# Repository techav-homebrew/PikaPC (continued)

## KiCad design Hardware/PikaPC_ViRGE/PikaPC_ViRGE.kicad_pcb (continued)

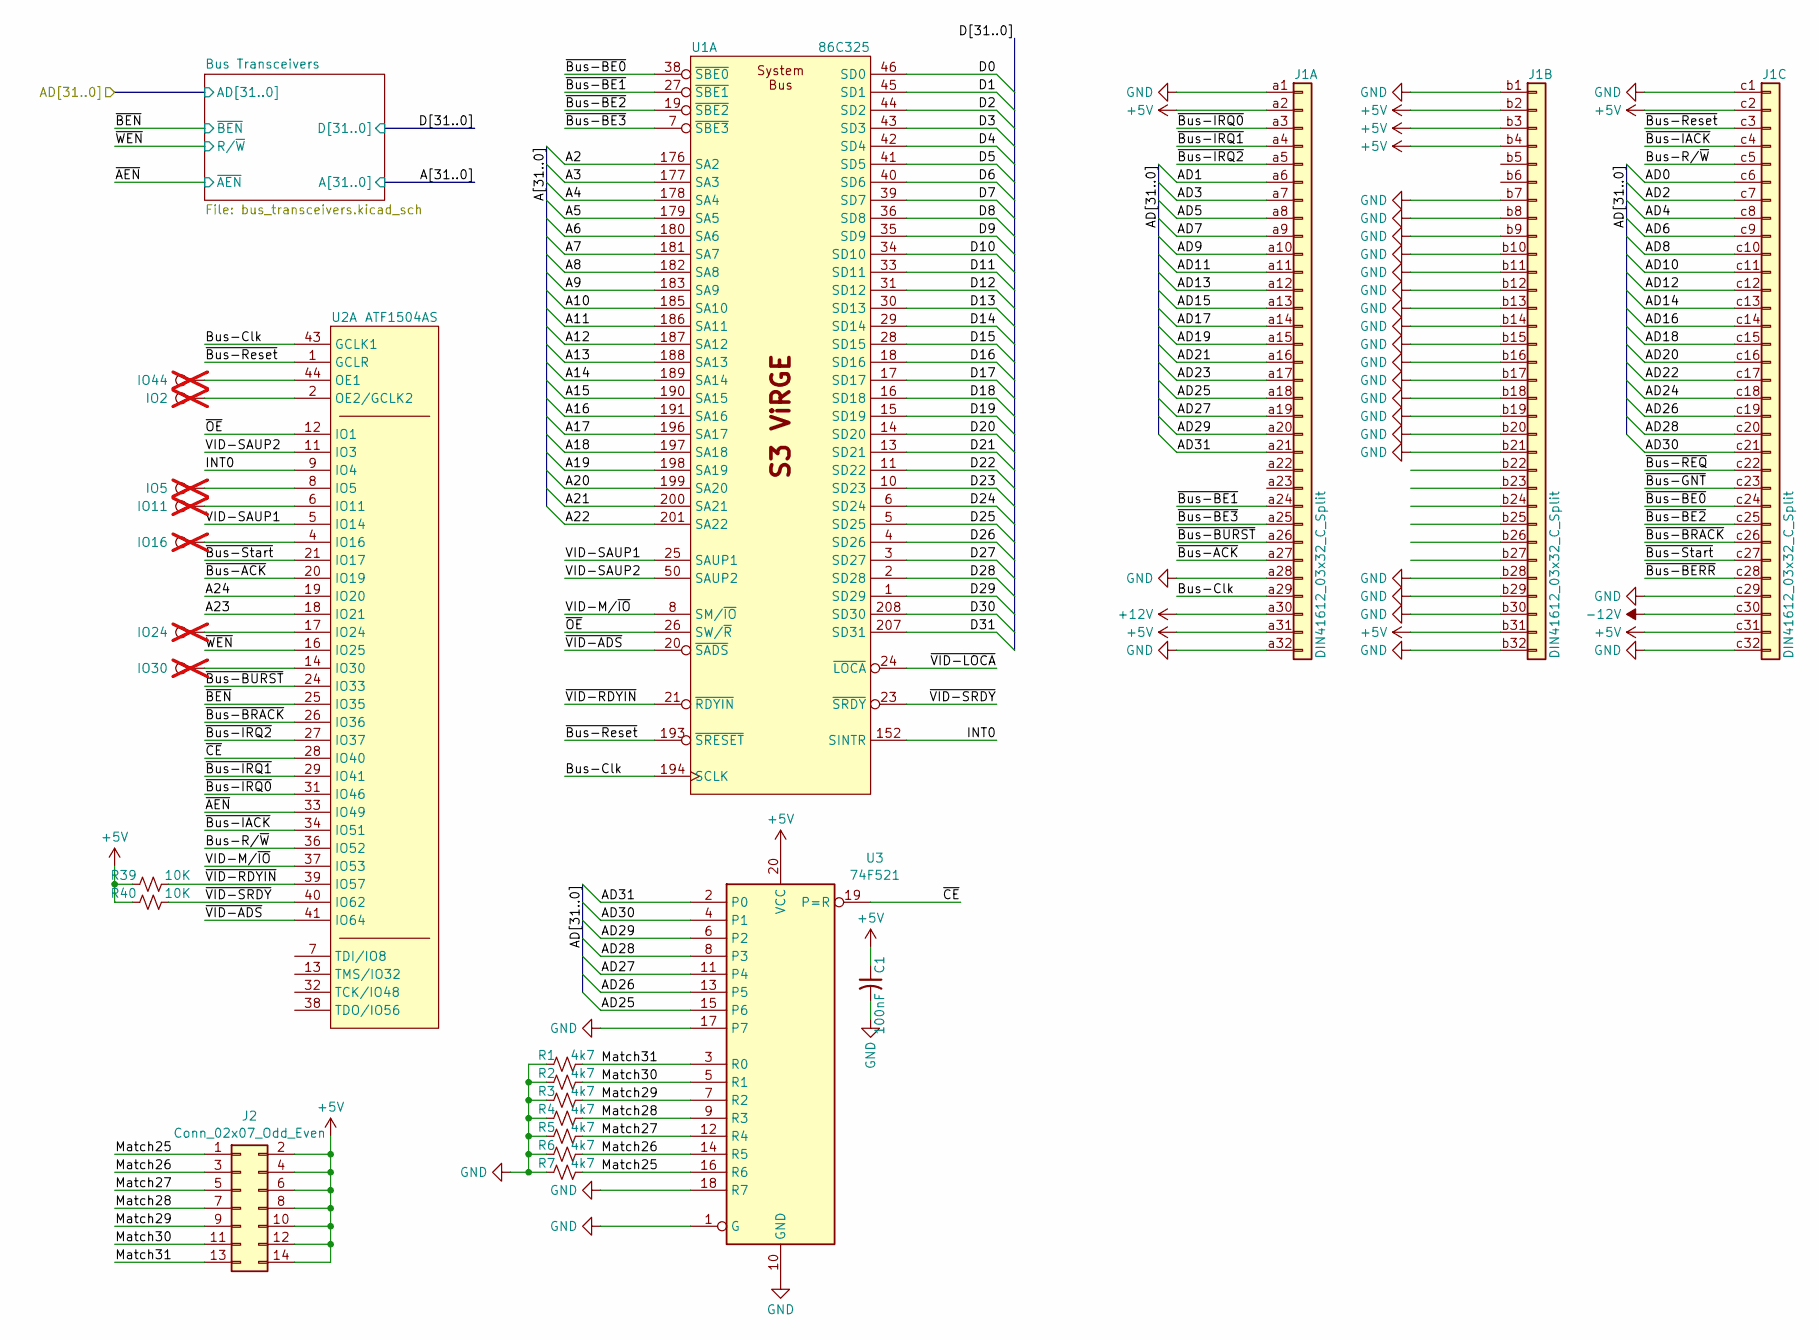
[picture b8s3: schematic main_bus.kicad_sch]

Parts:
C1: 100nF; C_0805_2012Metric; Mouser 187-CL21B104KACNNNC
IO2, IO5, IO11, IO16, IO24, IO30, IO44: TestPoint; PinHeader_1x01_P2.54mm_Vertical; not fitted
J1: DIN41612_03x32_C_Split; DIN41612_C_3x32_Male_Horizontal_THT
J2: Conn_02x07_Odd_Even; PinHeader_2x07_P2.54mm_Vertical
R1, R2, R3, R4, R5, R6, R7: 4k7; R_0805_2012Metric; Mouser 303-0805W8J0472T5E
R39, R40: 10K; R_0805_2012Metric; Mouser 303-0805S8J0103T5E
U1: 86C325; PQFP-208_28x28mm_P0.5mm
U2: ATF1504AS; PLCC-44_THT-Socket
U3: 74F521; SOIC-20W_7.5x12.8mm_P1.27mm; Mouser 595-SN74F521DWR

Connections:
+5V: C1.1, J1.a2, J1.a31, J1.b2, J1.b3, J1.b4, J1.b31, J1.c2, J1.c31, J2.2, J2.4, J2.6, J2.8, J2.10, J2.12, J2.14, R39.1, R40.1, U1.12 (Vdd), U1.37 (Vdd), U3.20 (VCC); also elsewhere on the board
+12V: J1.a30
-12V: J1.c30
/Main Bus/A2: U1.176 (SA2); also elsewhere on the board
/Main Bus/A3: U1.177 (SA3); also elsewhere on the board
/Main Bus/A4: U1.178 (SA4); also elsewhere on the board
/Main Bus/A5: U1.179 (SA5); also elsewhere on the board
/Main Bus/A6: U1.180 (SA6); also elsewhere on the board
/Main Bus/A7: U1.181 (SA7); also elsewhere on the board
/Main Bus/A8: U1.182 (SA8); also elsewhere on the board
/Main Bus/A9: U1.183 (SA9); also elsewhere on the board
/Main Bus/A10: U1.185 (SA10); also elsewhere on the board
/Main Bus/A11: U1.186 (SA11); also elsewhere on the board
/Main Bus/A12: U1.187 (SA12); also elsewhere on the board
/Main Bus/A13: U1.188 (SA13); also elsewhere on the board
/Main Bus/A14: U1.189 (SA14); also elsewhere on the board
/Main Bus/A15: U1.190 (SA15); also elsewhere on the board
/Main Bus/A16: U1.191 (SA16); also elsewhere on the board
/Main Bus/A17: U1.196 (SA17); also elsewhere on the board
/Main Bus/A18: U1.197 (SA18); also elsewhere on the board
/Main Bus/A19: U1.198 (SA19); also elsewhere on the board
/Main Bus/A20: U1.199 (SA20); also elsewhere on the board
/Main Bus/A21: U1.200 (SA21); also elsewhere on the board
/Main Bus/A22: U1.201 (SA22); also elsewhere on the board
/Main Bus/A23: U2.18 (IO21); also elsewhere on the board
/Main Bus/A24: U2.19 (IO20); also elsewhere on the board
/Main Bus/AD0: J1.c6; also elsewhere on the board
/Main Bus/AD1: J1.a6; also elsewhere on the board
/Main Bus/AD2: J1.c7; also elsewhere on the board
/Main Bus/AD3: J1.a7; also elsewhere on the board
/Main Bus/AD4: J1.c8; also elsewhere on the board
/Main Bus/AD5: J1.a8; also elsewhere on the board
/Main Bus/AD6: J1.c9; also elsewhere on the board
/Main Bus/AD7: J1.a9; also elsewhere on the board
/Main Bus/AD8: J1.c10; also elsewhere on the board
/Main Bus/AD9: J1.a10; also elsewhere on the board
/Main Bus/AD10: J1.c11; also elsewhere on the board
/Main Bus/AD11: J1.a11; also elsewhere on the board
/Main Bus/AD12: J1.c12; also elsewhere on the board
/Main Bus/AD13: J1.a12; also elsewhere on the board
/Main Bus/AD14: J1.c13; also elsewhere on the board
/Main Bus/AD15: J1.a13; also elsewhere on the board
/Main Bus/AD16: J1.c14; also elsewhere on the board
/Main Bus/AD17: J1.a14; also elsewhere on the board
/Main Bus/AD18: J1.c15; also elsewhere on the board
/Main Bus/AD19: J1.a15; also elsewhere on the board
/Main Bus/AD20: J1.c16; also elsewhere on the board
/Main Bus/AD21: J1.a16; also elsewhere on the board
/Main Bus/AD22: J1.c17; also elsewhere on the board
/Main Bus/AD23: J1.a17; also elsewhere on the board
/Main Bus/AD24: J1.c18; also elsewhere on the board
/Main Bus/AD25: J1.a18, U3.15 (P6); also elsewhere on the board
/Main Bus/AD26: J1.c19, U3.13 (P5); also elsewhere on the board
/Main Bus/AD27: J1.a19, U3.11 (P4); also elsewhere on the board
/Main Bus/AD28: J1.c20, U3.8 (P3); also elsewhere on the board
/Main Bus/AD29: J1.a20, U3.6 (P2); also elsewhere on the board
/Main Bus/AD30: J1.c21, U3.4 (P1); also elsewhere on the board
/Main Bus/AD31: J1.a21, U3.2 (P0); also elsewhere on the board
/Main Bus/Bus-Clk: J1.a29, U1.194 (SCLK), U2.43 (GCLK1)
/Main Bus/Bus-R/~W: J1.c5, U2.36 (IO52)
/Main Bus/D0: U1.46 (SD0); also elsewhere on the board
/Main Bus/D1: U1.45 (SD1); also elsewhere on the board
/Main Bus/D2: U1.44 (SD2); also elsewhere on the board
/Main Bus/D3: U1.43 (SD3); also elsewhere on the board
/Main Bus/D4: U1.42 (SD4); also elsewhere on the board
/Main Bus/D5: U1.41 (SD5); also elsewhere on the board
/Main Bus/D6: U1.40 (SD6); also elsewhere on the board
/Main Bus/D7: U1.39 (SD7); also elsewhere on the board
/Main Bus/D8: U1.36 (SD8); also elsewhere on the board
/Main Bus/D9: U1.35 (SD9); also elsewhere on the board
/Main Bus/D10: U1.34 (SD10); also elsewhere on the board
/Main Bus/D11: U1.33 (SD11); also elsewhere on the board
/Main Bus/D12: U1.31 (SD12); also elsewhere on the board
/Main Bus/D13: U1.30 (SD13); also elsewhere on the board
/Main Bus/D14: U1.29 (SD14); also elsewhere on the board
/Main Bus/D15: U1.28 (SD15); also elsewhere on the board
/Main Bus/D16: U1.18 (SD16); also elsewhere on the board
/Main Bus/D17: U1.17 (SD17); also elsewhere on the board
/Main Bus/D18: U1.16 (SD18); also elsewhere on the board
/Main Bus/D19: U1.15 (SD19); also elsewhere on the board
/Main Bus/D20: U1.14 (SD20); also elsewhere on the board
/Main Bus/D21: U1.13 (SD21); also elsewhere on the board
/Main Bus/D22: U1.11 (SD22); also elsewhere on the board
/Main Bus/D23: U1.10 (SD23); also elsewhere on the board
/Main Bus/D24: U1.6 (SD24); also elsewhere on the board
/Main Bus/D25: U1.5 (SD25); also elsewhere on the board
/Main Bus/D26: U1.4 (SD26); also elsewhere on the board
/Main Bus/D27: U1.3 (SD27); also elsewhere on the board
/Main Bus/D28: U1.2 (SD28); also elsewhere on the board
/Main Bus/D29: U1.1 (SD29); also elsewhere on the board
/Main Bus/D30: U1.208 (SD30); also elsewhere on the board
/Main Bus/D31: U1.207 (SD31); also elsewhere on the board
/Main Bus/INT0: U1.152 (SINTR), U2.9 (IO4)
/Main Bus/Match25: J2.1, R7.2, U3.16 (R6)
/Main Bus/Match26: J2.3, R6.2, U3.14 (R5)
/Main Bus/Match27: J2.5, R5.2, U3.12 (R4)
/Main Bus/Match28: J2.7, R4.2, U3.9 (R3)
/Main Bus/Match29: J2.9, R3.2, U3.7 (R2)
/Main Bus/Match30: J2.11, R2.2, U3.5 (R1)
/Main Bus/Match31: J2.13, R1.2, U3.3 (R0)
/Main Bus/VID-M/~IO: U1.8 (SM/~IO), U2.37 (IO53)
/Main Bus/VID-SAUP1: U1.25 (SAUP1), U2.5 (IO14)
/Main Bus/VID-SAUP2: U1.50 (SAUP2), U2.11 (IO3)
/Main Bus/~AEN: U2.33 (IO49); also elsewhere on the board
/Main Bus/~BEN: U2.25 (IO35); also elsewhere on the board
/Main Bus/~Bus-ACK: J1.a27, U2.20 (IO19)
/Main Bus/~Bus-BE0: J1.c24, U1.38 (~SBE0)
/Main Bus/~Bus-BE1: J1.a24, U1.27 (~SBE1)
/Main Bus/~Bus-BE2: J1.c25, U1.19 (~SBE2)
/Main Bus/~Bus-BE3: J1.a25, U1.7 (~SBE3)
/Main Bus/~Bus-BERR: J1.c28
/Main Bus/~Bus-BRACK: J1.c26, U2.26 (IO36)
/Main Bus/~Bus-BURST: J1.a26, U2.24 (IO33)
/Main Bus/~Bus-GNT: J1.c23
/Main Bus/~Bus-IACK: J1.c4, U2.34 (IO51)
/Main Bus/~Bus-IRQ0: J1.a3, U2.31 (IO46)
/Main Bus/~Bus-IRQ1: J1.a4, U2.29 (IO41)
/Main Bus/~Bus-IRQ2: J1.a5, U2.27 (IO37)
/Main Bus/~Bus-REQ: J1.c22
/Main Bus/~Bus-Reset: J1.c3, U1.193 (~SRESET), U2.1 (GCLR)
/Main Bus/~Bus-Start: J1.c27, U2.21 (IO17)
/Main Bus/~CE: U2.28 (IO40), U3.19 (P=R)
/Main Bus/~OE: U1.26 (SW/~R), U2.12 (IO1)
/Main Bus/~VID-ADS: U1.20 (~SADS), U2.41 (IO64)
/Main Bus/~VID-LOCA: U1.24 (~LOCA); also elsewhere on the board
/Main Bus/~VID-RDYIN: R39.2, U1.21 (~RDYIN), U2.39 (IO57)
/Main Bus/~VID-SRDY: R40.2, U1.23 (~SRDY), U2.40 (IO62)
/Main Bus/~WEN: U2.16 (IO25); also elsewhere on the board
GND: C1.2, J1.a1, J1.a28, J1.a32, J1.b1, J1.b7, J1.b8, J1.b9, J1.b10, J1.b11, J1.b12, J1.b13, J1.b14, J1.b15, J1.b16, J1.b17, J1.b18, J1.b19, J1.b20, J1.b21, J1.b28, J1.b29, J1.b30, J1.b32, J1.c1, J1.c29, J1.c32, R1.1, R2.1, R3.1, R4.1, R5.1, R6.1, R7.1, U1.9 (Vss), U1.32 (Vss), U3.1 (G), U3.10 (GND), U3.17 (P7), U3.18 (R7); also elsewhere on the board
unnamed: IO5.1, U2.8 (IO5)
unnamed: IO11.1, U2.6 (IO11)
unnamed: IO16.1, U2.4 (IO16)
unnamed: IO24.1, U2.17 (IO24)
unnamed: IO30.1, U2.14 (IO30)
unnamed: IO44.1, U2.44 (OE1)
unnamed: IO2.1, U2.2 (OE2/GCLK2)

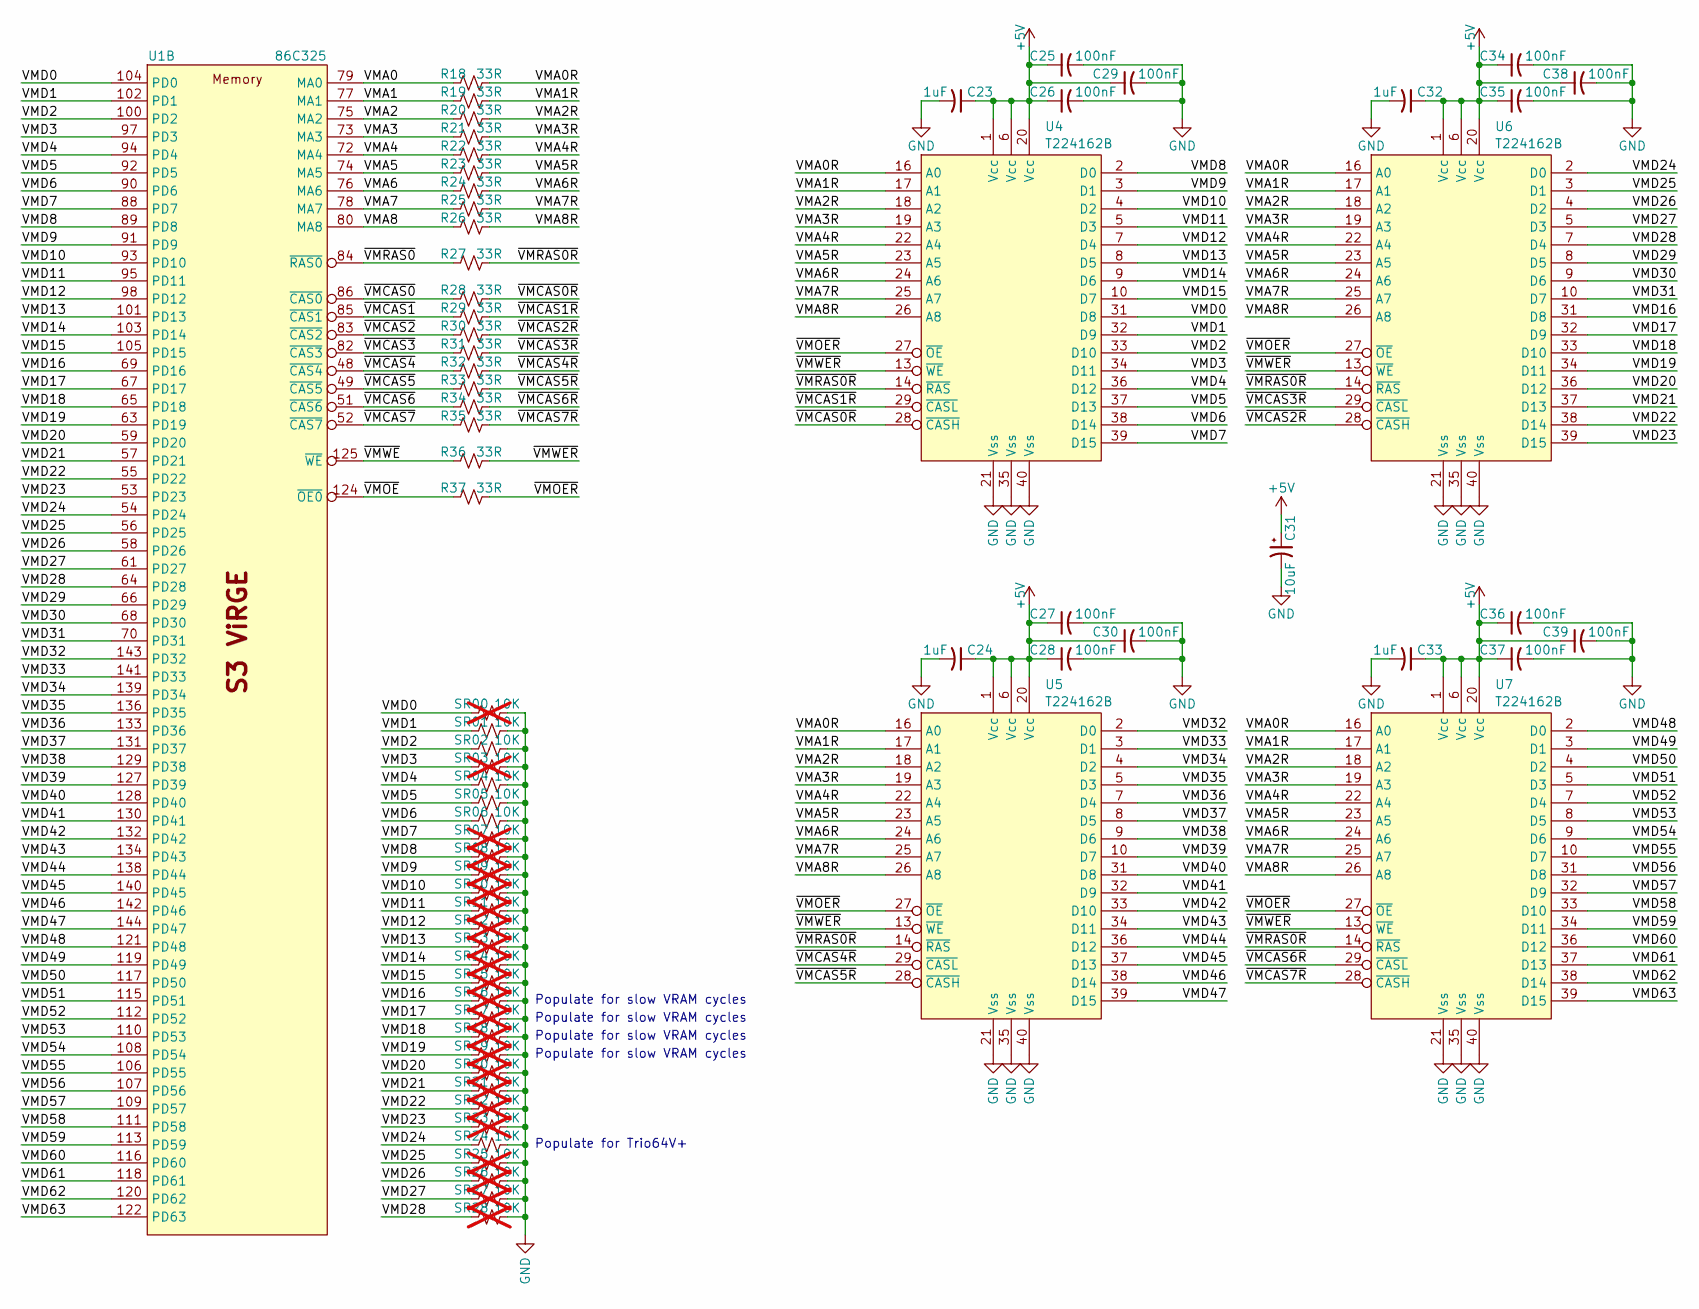
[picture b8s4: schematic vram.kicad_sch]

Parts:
C23, C24, C32, C33: 1uF; C_0805_2012Metric
C25, C26, C27, C28, C29, C30, C34, C35, C36, C37, C38, C39: 100nF; C_0805_2012Metric
C31: 10uF; CP_Elec_4x5.7; Mouser 80-EDK106M016A9BAA
R18, R19, R20, R21, R22, R23, R24, R25, R26, R27, R28, R29, R30, R31, R32, R33, R34, R35, R36, R37: 33R; R_0805_2012Metric
SR00, SR03, SR07, SR08, SR09, SR10, SR11, SR12, SR13, SR14, SR15, SR16, SR17, SR18, SR19, SR20, SR21, SR22, SR23, SR25, SR26, SR27, SR28: 10K; R_0805_2012Metric; not fitted
SR01, SR02, SR04, SR05, SR06, SR24: 10K; R_0805_2012Metric
U1: 86C325; PQFP-208_28x28mm_P0.5mm
U4, U5, U6, U7: T224162B; SOJ-44_10.16x28.575mm_P1.27mm

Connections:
+5V: C23.1, C24.1, C25.1, C26.1, C27.1, C28.1, C29.1, C30.1, C31.1, C32.1, C33.1, C34.1, C35.1, C36.1, C37.1, C38.1, C39.1, U4.1 (Vcc), U4.6 (Vcc), U4.20 (Vcc), U5.1 (Vcc), U5.6 (Vcc), U5.20 (Vcc), U6.1 (Vcc), U6.6 (Vcc), U6.20 (Vcc), U7.1 (Vcc), U7.6 (Vcc), U7.20 (Vcc); also elsewhere on the board
/VRAM/VMA0: R18.1, U1.79 (MA0)
/VRAM/VMA0R: R18.2, U4.16 (A0), U5.16 (A0), U6.16 (A0), U7.16 (A0)
/VRAM/VMA1: R19.1, U1.77 (MA1)
/VRAM/VMA1R: R19.2, U4.17 (A1), U5.17 (A1), U6.17 (A1), U7.17 (A1)
/VRAM/VMA2: R20.1, U1.75 (MA2)
/VRAM/VMA2R: R20.2, U4.18 (A2), U5.18 (A2), U6.18 (A2), U7.18 (A2)
/VRAM/VMA3: R21.1, U1.73 (MA3)
/VRAM/VMA3R: R21.2, U4.19 (A3), U5.19 (A3), U6.19 (A3), U7.19 (A3)
/VRAM/VMA4: R22.1, U1.72 (MA4)
/VRAM/VMA4R: R22.2, U4.22 (A4), U5.22 (A4), U6.22 (A4), U7.22 (A4)
/VRAM/VMA5: R23.1, U1.74 (MA5)
/VRAM/VMA5R: R23.2, U4.23 (A5), U5.23 (A5), U6.23 (A5), U7.23 (A5)
/VRAM/VMA6: R24.1, U1.76 (MA6)
/VRAM/VMA6R: R24.2, U4.24 (A6), U5.24 (A6), U6.24 (A6), U7.24 (A6)
/VRAM/VMA7: R25.1, U1.78 (MA7)
/VRAM/VMA7R: R25.2, U4.25 (A7), U5.25 (A7), U6.25 (A7), U7.25 (A7)
/VRAM/VMA8: R26.1, U1.80 (MA8)
/VRAM/VMA8R: R26.2, U4.26 (A8), U5.26 (A8), U6.26 (A8), U7.26 (A8)
/VRAM/VMD0: SR00.1, U1.104 (PD0), U4.31 (D8)
/VRAM/VMD1: SR01.1, U1.102 (PD1), U4.32 (D9)
/VRAM/VMD2: SR02.1, U1.100 (PD2), U4.33 (D10)
/VRAM/VMD3: SR03.1, U1.97 (PD3), U4.34 (D11)
/VRAM/VMD4: SR04.1, U1.94 (PD4), U4.36 (D12)
/VRAM/VMD5: SR05.1, U1.92 (PD5), U4.37 (D13)
/VRAM/VMD6: SR06.1, U1.90 (PD6), U4.38 (D14)
/VRAM/VMD7: SR07.1, U1.88 (PD7), U4.39 (D15)
/VRAM/VMD8: SR08.1, U1.89 (PD8), U4.2 (D0)
/VRAM/VMD9: SR09.1, U1.91 (PD9), U4.3 (D1)
/VRAM/VMD10: SR10.1, U1.93 (PD10), U4.4 (D2)
/VRAM/VMD11: SR11.1, U1.95 (PD11), U4.5 (D3)
/VRAM/VMD12: SR12.1, U1.98 (PD12), U4.7 (D4)
/VRAM/VMD13: SR13.1, U1.101 (PD13), U4.8 (D5)
/VRAM/VMD14: SR14.1, U1.103 (PD14), U4.9 (D6)
/VRAM/VMD15: SR15.1, U1.105 (PD15), U4.10 (D7)
/VRAM/VMD16: SR16.1, U1.69 (PD16), U6.31 (D8)
/VRAM/VMD17: SR17.1, U1.67 (PD17), U6.32 (D9)
/VRAM/VMD18: SR18.1, U1.65 (PD18), U6.33 (D10)
/VRAM/VMD19: SR19.1, U1.63 (PD19), U6.34 (D11)
/VRAM/VMD20: SR20.1, U1.59 (PD20), U6.36 (D12)
/VRAM/VMD21: SR21.1, U1.57 (PD21), U6.37 (D13)
/VRAM/VMD22: SR22.1, U1.55 (PD22), U6.38 (D14)
/VRAM/VMD23: SR23.1, U1.53 (PD23), U6.39 (D15)
/VRAM/VMD24: SR24.1, U1.54 (PD24), U6.2 (D0)
/VRAM/VMD25: SR25.1, U1.56 (PD25), U6.3 (D1)
/VRAM/VMD26: SR26.1, U1.58 (PD26), U6.4 (D2)
/VRAM/VMD27: SR27.1, U1.61 (PD27), U6.5 (D3)
/VRAM/VMD28: SR28.1, U1.64 (PD28), U6.7 (D4)
/VRAM/VMD29: U1.66 (PD29), U6.8 (D5)
/VRAM/VMD30: U1.68 (PD30), U6.9 (D6)
/VRAM/VMD31: U1.70 (PD31), U6.10 (D7)
/VRAM/VMD32: U1.143 (PD32), U5.2 (D0)
/VRAM/VMD33: U1.141 (PD33), U5.3 (D1)
/VRAM/VMD34: U1.139 (PD34), U5.4 (D2)
/VRAM/VMD35: U1.136 (PD35), U5.5 (D3)
/VRAM/VMD36: U1.133 (PD36), U5.7 (D4)
/VRAM/VMD37: U1.131 (PD37), U5.8 (D5)
/VRAM/VMD38: U1.129 (PD38), U5.9 (D6)
/VRAM/VMD39: U1.127 (PD39), U5.10 (D7)
/VRAM/VMD40: U1.128 (PD40), U5.31 (D8)
/VRAM/VMD41: U1.130 (PD41), U5.32 (D9)
/VRAM/VMD42: U1.132 (PD42), U5.33 (D10)
/VRAM/VMD43: U1.134 (PD43), U5.34 (D11)
/VRAM/VMD44: U1.138 (PD44), U5.36 (D12)
/VRAM/VMD45: U1.140 (PD45), U5.37 (D13)
/VRAM/VMD46: U1.142 (PD46), U5.38 (D14)
/VRAM/VMD47: U1.144 (PD47), U5.39 (D15)
/VRAM/VMD48: U1.121 (PD48), U7.2 (D0)
/VRAM/VMD49: U1.119 (PD49), U7.3 (D1)
/VRAM/VMD50: U1.117 (PD50), U7.4 (D2)
/VRAM/VMD51: U1.115 (PD51), U7.5 (D3)
/VRAM/VMD52: U1.112 (PD52), U7.7 (D4)
/VRAM/VMD53: U1.110 (PD53), U7.8 (D5)
/VRAM/VMD54: U1.108 (PD54), U7.9 (D6)
/VRAM/VMD55: U1.106 (PD55), U7.10 (D7)
/VRAM/VMD56: U1.107 (PD56), U7.31 (D8)
/VRAM/VMD57: U1.109 (PD57), U7.32 (D9)
/VRAM/VMD58: U1.111 (PD58), U7.33 (D10)
/VRAM/VMD59: U1.113 (PD59), U7.34 (D11)
/VRAM/VMD60: U1.116 (PD60), U7.36 (D12)
/VRAM/VMD61: U1.118 (PD61), U7.37 (D13)
/VRAM/VMD62: U1.120 (PD62), U7.38 (D14)
/VRAM/VMD63: U1.122 (PD63), U7.39 (D15)
/VRAM/~VMCAS0R: R28.2, U4.28 (~CASH)
/VRAM/~VMCAS0: R28.1, U1.86 (~CAS0)
/VRAM/~VMCAS1R: R29.2, U4.29 (~CASL)
/VRAM/~VMCAS1: R29.1, U1.85 (~CAS1)
/VRAM/~VMCAS2R: R30.2, U6.28 (~CASH)
/VRAM/~VMCAS2: R30.1, U1.83 (~CAS2)
/VRAM/~VMCAS3R: R31.2, U6.29 (~CASL)
/VRAM/~VMCAS3: R31.1, U1.82 (~CAS3)
/VRAM/~VMCAS4R: R32.2, U5.29 (~CASL)
/VRAM/~VMCAS4: R32.1, U1.48 (~CAS4)
/VRAM/~VMCAS5R: R33.2, U5.28 (~CASH)
/VRAM/~VMCAS5: R33.1, U1.49 (~CAS5)
/VRAM/~VMCAS6R: R34.2, U7.29 (~CASL)
/VRAM/~VMCAS6: R34.1, U1.51 (~CAS6)
/VRAM/~VMCAS7R: R35.2, U7.28 (~CASH)
/VRAM/~VMCAS7: R35.1, U1.52 (~CAS7)
/VRAM/~VMOER: R37.2, U4.27 (~OE), U5.27 (~OE), U6.27 (~OE), U7.27 (~OE)
/VRAM/~VMOE: R37.1, U1.124 (~OE0)
/VRAM/~VMRAS0R: R27.2, U4.14 (~RAS), U5.14 (~RAS), U6.14 (~RAS), U7.14 (~RAS)
/VRAM/~VMRAS0: R27.1, U1.84 (~RAS0)
/VRAM/~VMWER: R36.2, U4.13 (~WE), U5.13 (~WE), U6.13 (~WE), U7.13 (~WE)
/VRAM/~VMWE: R36.1, U1.125 (~WE)
GND: C23.2, C24.2, C25.2, C26.2, C27.2, C28.2, C29.2, C30.2, C31.2, C32.2, C33.2, C34.2, C35.2, C36.2, C37.2, C38.2, C39.2, SR00.2, SR01.2, SR02.2, SR03.2, SR04.2, SR05.2, SR06.2, SR07.2, SR08.2, SR09.2, SR10.2, SR11.2, SR12.2, SR13.2, SR14.2, SR15.2, SR16.2, SR17.2, SR18.2, SR19.2, SR20.2, SR21.2, SR22.2, SR23.2, SR24.2, SR25.2, SR26.2, SR27.2, SR28.2, U4.21 (Vss), U4.35 (Vss), U4.40 (Vss), U5.21 (Vss), U5.35 (Vss), U5.40 (Vss), U6.21 (Vss), U6.35 (Vss), U6.40 (Vss), U7.21 (Vss), U7.35 (Vss), U7.40 (Vss); also elsewhere on the board

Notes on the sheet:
Populate for slow VRAM cycles
Populate for Trio64V+

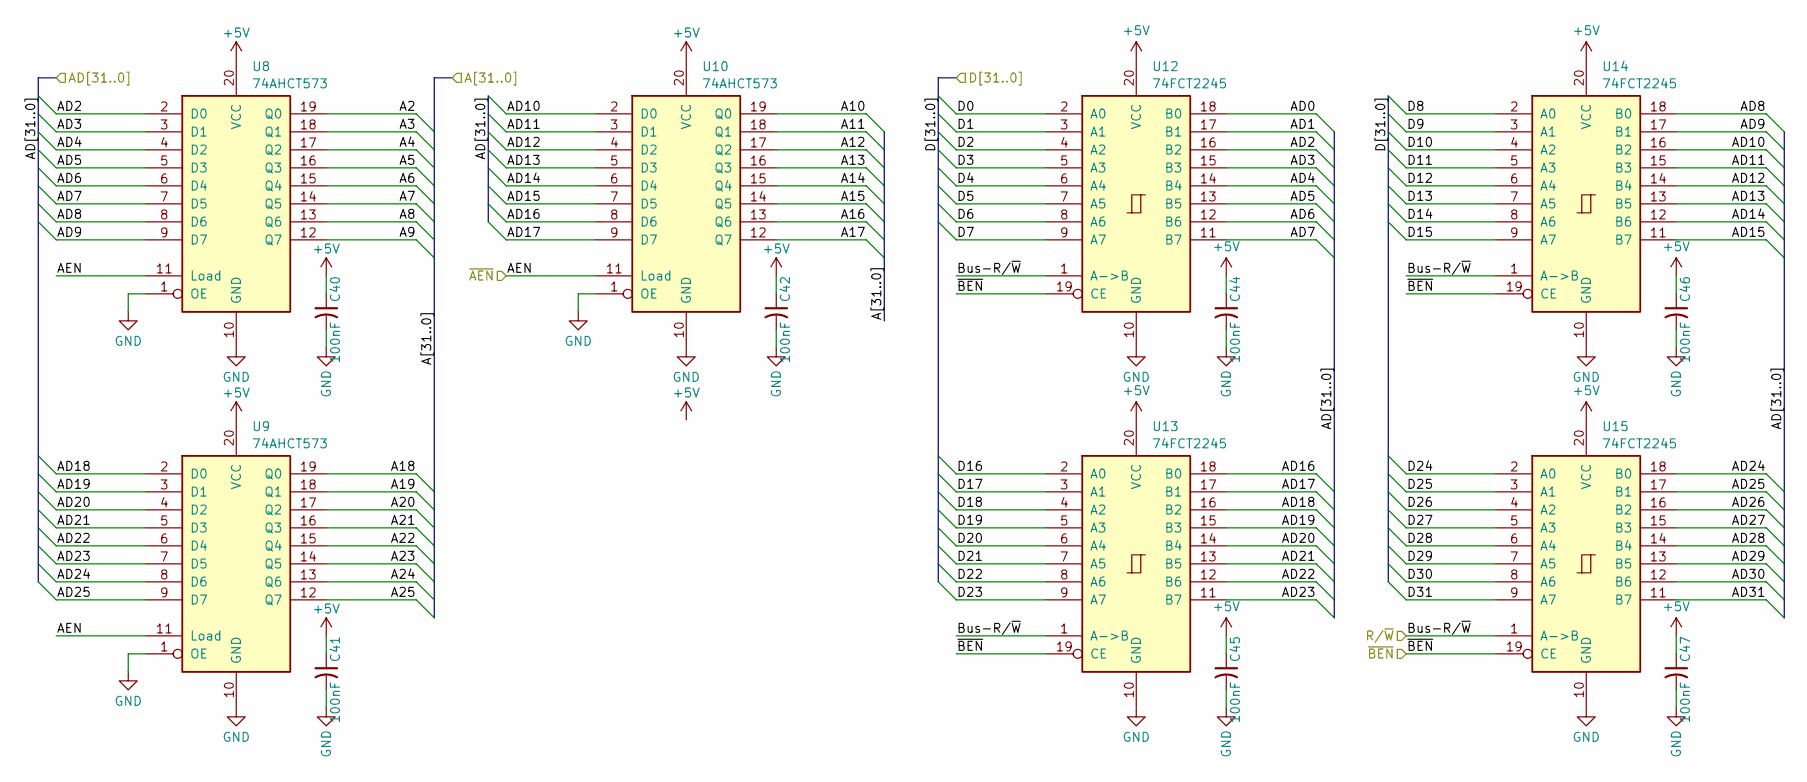
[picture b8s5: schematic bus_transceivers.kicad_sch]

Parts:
C40, C41, C42, C44, C45, C46, C47: 100nF; C_0805_2012Metric
U8, U9, U10: 74AHCT573; TSSOP-20_4.4x6.5mm_P0.65mm; Mouser 771-74AHCT573PW-T
U12, U13, U14, U15: 74FCT2245; SOIC-20W_7.5x12.8mm_P1.27mm

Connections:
+5V: C40.1, C41.1, C42.1, C44.1, C45.1, C46.1, C47.1, U8.20 (VCC), U9.20 (VCC), U10.20 (VCC), U12.20 (VCC), U13.20 (VCC), U14.20 (VCC), U15.20 (VCC); also elsewhere on the board
/Main Bus/A2: U8.19 (Q0); also elsewhere on the board
/Main Bus/A3: U8.18 (Q1); also elsewhere on the board
/Main Bus/A4: U8.17 (Q2); also elsewhere on the board
/Main Bus/A5: U8.16 (Q3); also elsewhere on the board
/Main Bus/A6: U8.15 (Q4); also elsewhere on the board
/Main Bus/A7: U8.14 (Q5); also elsewhere on the board
/Main Bus/A8: U8.13 (Q6); also elsewhere on the board
/Main Bus/A9: U8.12 (Q7); also elsewhere on the board
/Main Bus/A10: U10.19 (Q0); also elsewhere on the board
/Main Bus/A11: U10.18 (Q1); also elsewhere on the board
/Main Bus/A12: U10.17 (Q2); also elsewhere on the board
/Main Bus/A13: U10.16 (Q3); also elsewhere on the board
/Main Bus/A14: U10.15 (Q4); also elsewhere on the board
/Main Bus/A15: U10.14 (Q5); also elsewhere on the board
/Main Bus/A16: U10.13 (Q6); also elsewhere on the board
/Main Bus/A17: U10.12 (Q7); also elsewhere on the board
/Main Bus/A18: U9.19 (Q0); also elsewhere on the board
/Main Bus/A19: U9.18 (Q1); also elsewhere on the board
/Main Bus/A20: U9.17 (Q2); also elsewhere on the board
/Main Bus/A21: U9.16 (Q3); also elsewhere on the board
/Main Bus/A22: U9.15 (Q4); also elsewhere on the board
/Main Bus/A23: U9.14 (Q5); also elsewhere on the board
/Main Bus/A24: U9.13 (Q6); also elsewhere on the board
/Main Bus/A25: U9.12 (Q7)
/Main Bus/AD0: U12.18 (B0); also elsewhere on the board
/Main Bus/AD1: U12.17 (B1); also elsewhere on the board
/Main Bus/AD2: U8.2 (D0), U12.16 (B2); also elsewhere on the board
/Main Bus/AD3: U8.3 (D1), U12.15 (B3); also elsewhere on the board
/Main Bus/AD4: U8.4 (D2), U12.14 (B4); also elsewhere on the board
/Main Bus/AD5: U8.5 (D3), U12.13 (B5); also elsewhere on the board
/Main Bus/AD6: U8.6 (D4), U12.12 (B6); also elsewhere on the board
/Main Bus/AD7: U8.7 (D5), U12.11 (B7); also elsewhere on the board
/Main Bus/AD8: U8.8 (D6), U14.18 (B0); also elsewhere on the board
/Main Bus/AD9: U8.9 (D7), U14.17 (B1); also elsewhere on the board
/Main Bus/AD10: U10.2 (D0), U14.16 (B2); also elsewhere on the board
/Main Bus/AD11: U10.3 (D1), U14.15 (B3); also elsewhere on the board
/Main Bus/AD12: U10.4 (D2), U14.14 (B4); also elsewhere on the board
/Main Bus/AD13: U10.5 (D3), U14.13 (B5); also elsewhere on the board
/Main Bus/AD14: U10.6 (D4), U14.12 (B6); also elsewhere on the board
/Main Bus/AD15: U10.7 (D5), U14.11 (B7); also elsewhere on the board
/Main Bus/AD16: U10.8 (D6), U13.18 (B0); also elsewhere on the board
/Main Bus/AD17: U10.9 (D7), U13.17 (B1); also elsewhere on the board
/Main Bus/AD18: U9.2 (D0), U13.16 (B2); also elsewhere on the board
/Main Bus/AD19: U9.3 (D1), U13.15 (B3); also elsewhere on the board
/Main Bus/AD20: U9.4 (D2), U13.14 (B4); also elsewhere on the board
/Main Bus/AD21: U9.5 (D3), U13.13 (B5); also elsewhere on the board
/Main Bus/AD22: U9.6 (D4), U13.12 (B6); also elsewhere on the board
/Main Bus/AD23: U9.7 (D5), U13.11 (B7); also elsewhere on the board
/Main Bus/AD24: U9.8 (D6), U15.18 (B0); also elsewhere on the board
/Main Bus/AD25: U9.9 (D7), U15.17 (B1); also elsewhere on the board
/Main Bus/AD26: U15.16 (B2); also elsewhere on the board
/Main Bus/AD27: U15.15 (B3); also elsewhere on the board
/Main Bus/AD28: U15.14 (B4); also elsewhere on the board
/Main Bus/AD29: U15.13 (B5); also elsewhere on the board
/Main Bus/AD30: U15.12 (B6); also elsewhere on the board
/Main Bus/AD31: U15.11 (B7); also elsewhere on the board
/Main Bus/D0: U12.2 (A0); also elsewhere on the board
/Main Bus/D1: U12.3 (A1); also elsewhere on the board
/Main Bus/D2: U12.4 (A2); also elsewhere on the board
/Main Bus/D3: U12.5 (A3); also elsewhere on the board
/Main Bus/D4: U12.6 (A4); also elsewhere on the board
/Main Bus/D5: U12.7 (A5); also elsewhere on the board
/Main Bus/D6: U12.8 (A6); also elsewhere on the board
/Main Bus/D7: U12.9 (A7); also elsewhere on the board
/Main Bus/D8: U14.2 (A0); also elsewhere on the board
/Main Bus/D9: U14.3 (A1); also elsewhere on the board
/Main Bus/D10: U14.4 (A2); also elsewhere on the board
/Main Bus/D11: U14.5 (A3); also elsewhere on the board
/Main Bus/D12: U14.6 (A4); also elsewhere on the board
/Main Bus/D13: U14.7 (A5); also elsewhere on the board
/Main Bus/D14: U14.8 (A6); also elsewhere on the board
/Main Bus/D15: U14.9 (A7); also elsewhere on the board
/Main Bus/D16: U13.2 (A0); also elsewhere on the board
/Main Bus/D17: U13.3 (A1); also elsewhere on the board
/Main Bus/D18: U13.4 (A2); also elsewhere on the board
/Main Bus/D19: U13.5 (A3); also elsewhere on the board
/Main Bus/D20: U13.6 (A4); also elsewhere on the board
/Main Bus/D21: U13.7 (A5); also elsewhere on the board
/Main Bus/D22: U13.8 (A6); also elsewhere on the board
/Main Bus/D23: U13.9 (A7); also elsewhere on the board
/Main Bus/D24: U15.2 (A0); also elsewhere on the board
/Main Bus/D25: U15.3 (A1); also elsewhere on the board
/Main Bus/D26: U15.4 (A2); also elsewhere on the board
/Main Bus/D27: U15.5 (A3); also elsewhere on the board
/Main Bus/D28: U15.6 (A4); also elsewhere on the board
/Main Bus/D29: U15.7 (A5); also elsewhere on the board
/Main Bus/D30: U15.8 (A6); also elsewhere on the board
/Main Bus/D31: U15.9 (A7); also elsewhere on the board
/Main Bus/~AEN: U8.11 (Load), U9.11 (Load), U10.11 (Load); also elsewhere on the board
/Main Bus/~BEN: U12.19 (CE), U13.19 (CE), U14.19 (CE), U15.19 (CE); also elsewhere on the board
/Main Bus/~WEN: U12.1 (A->B), U13.1 (A->B), U14.1 (A->B), U15.1 (A->B); also elsewhere on the board
GND: C40.2, C41.2, C42.2, C44.2, C45.2, C46.2, C47.2, U8.1 (OE), U8.10 (GND), U9.1 (OE), U9.10 (GND), U10.1 (OE), U10.10 (GND), U12.10 (GND), U13.10 (GND), U14.10 (GND), U15.10 (GND); also elsewhere on the board

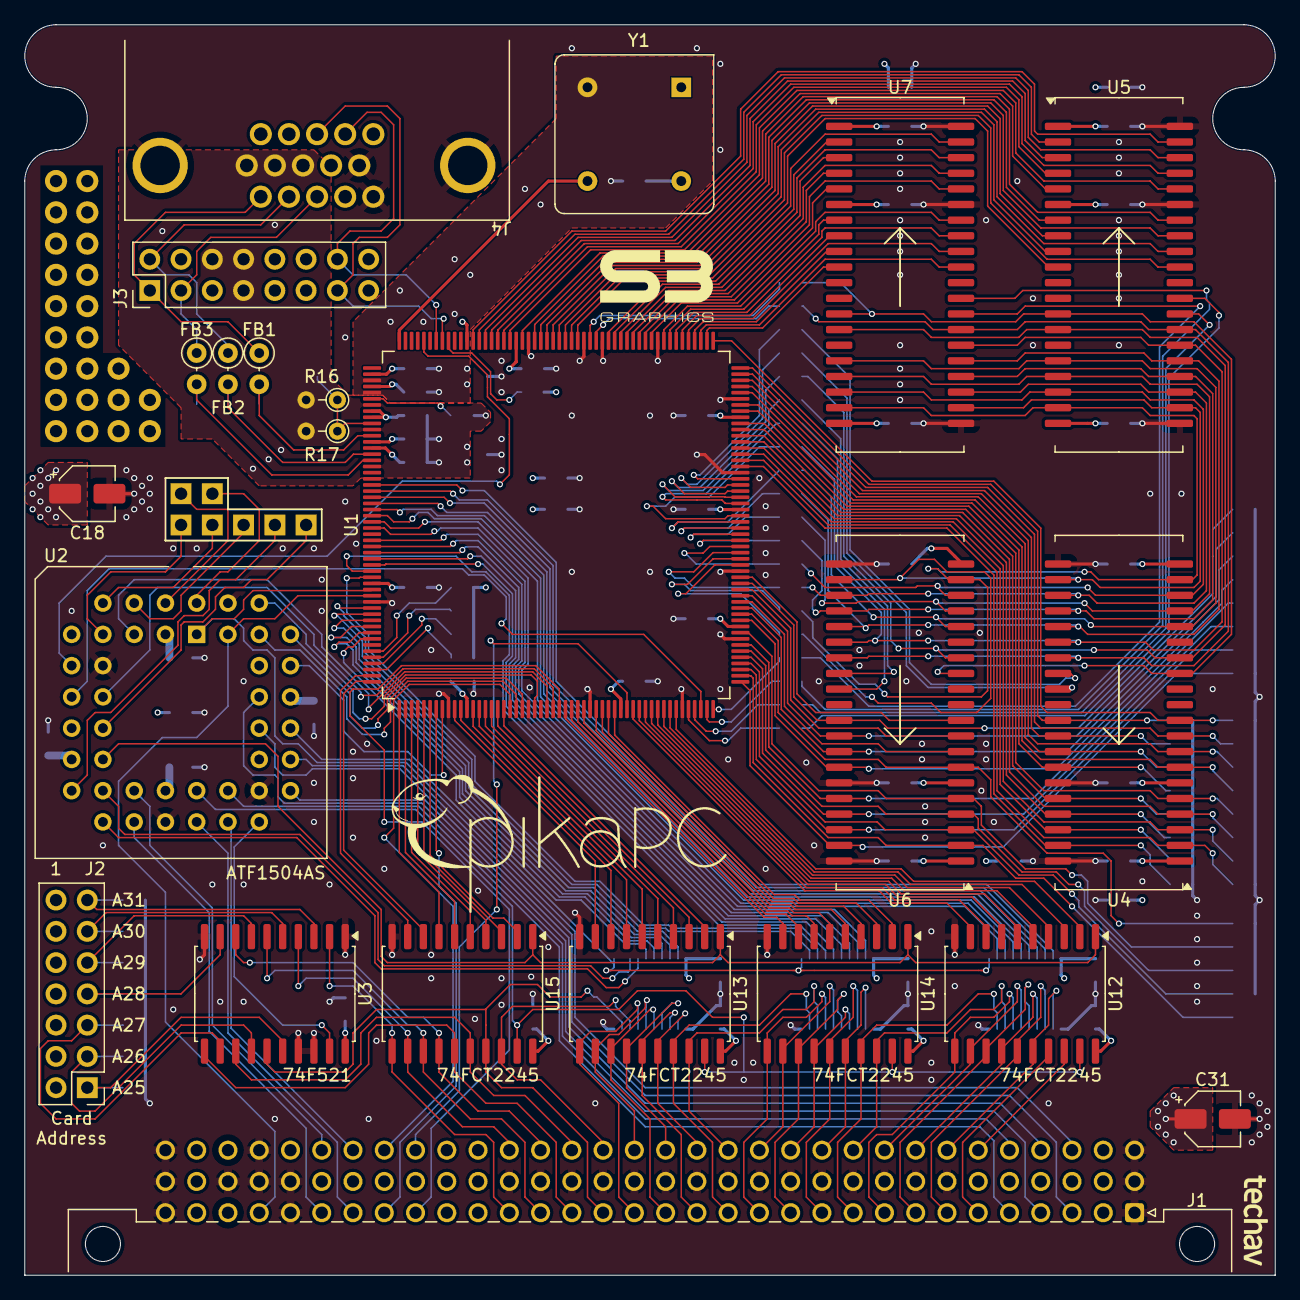
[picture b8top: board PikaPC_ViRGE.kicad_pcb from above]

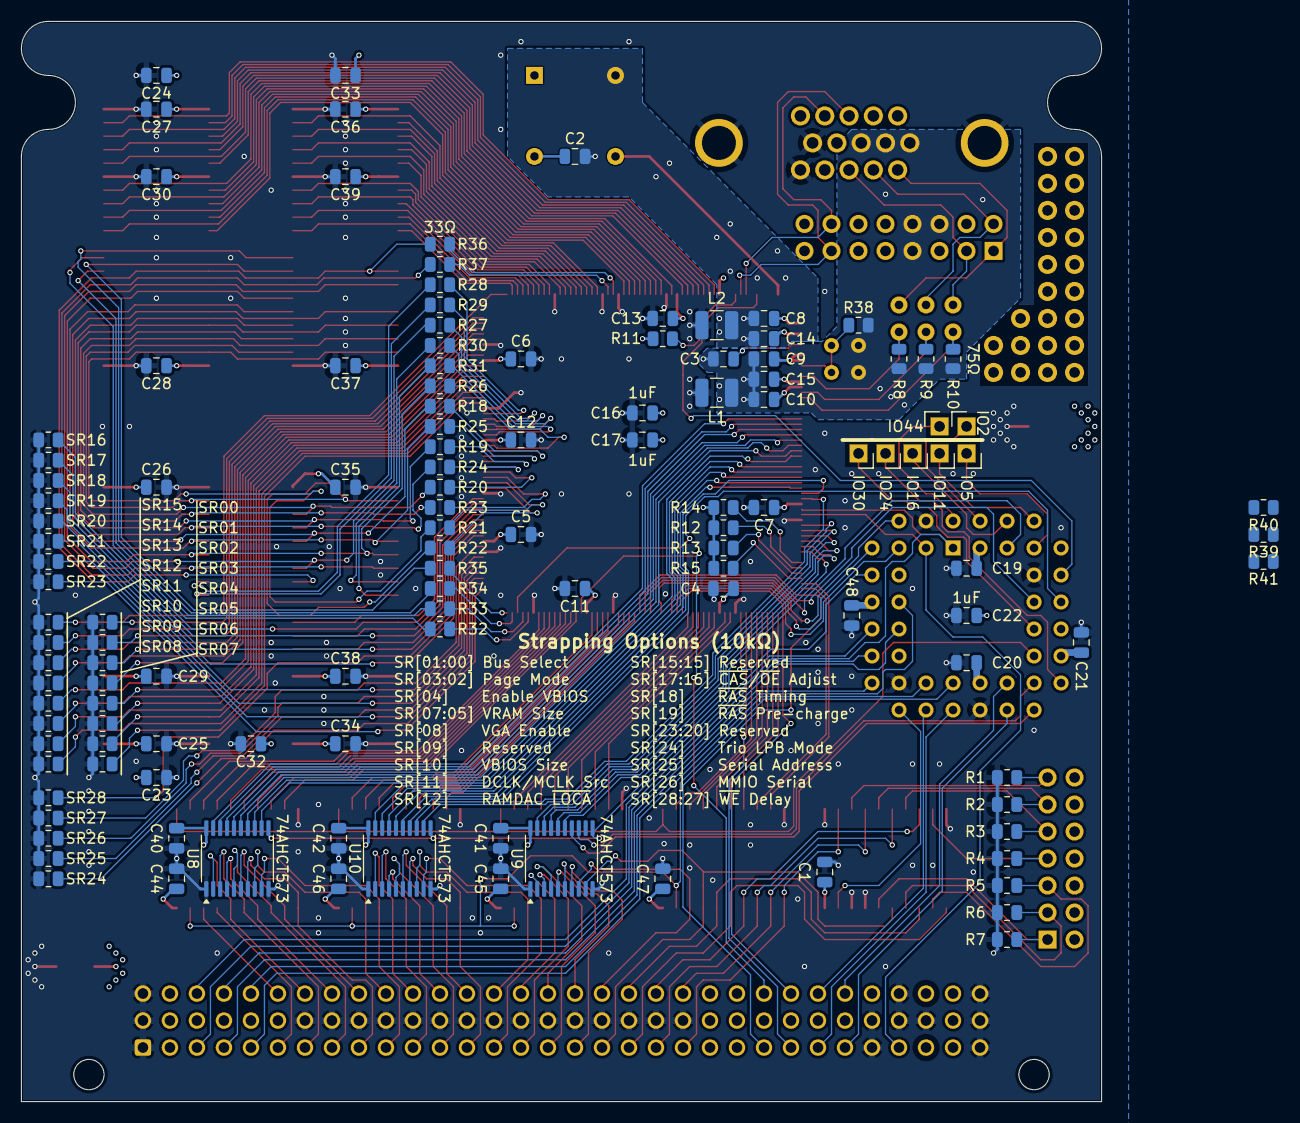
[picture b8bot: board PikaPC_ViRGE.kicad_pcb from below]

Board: 4 copper layers, 101.6 x 101.6 mm, 148 parts (125 on the bottom side), 253 nets.

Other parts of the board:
R38: 147R; R_0805_2012Metric
R41: 10K; R_0805_2012Metric

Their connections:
+5V: R41.2; also elsewhere on the board
/Main Bus/~VID-LOCA: R41.1; also elsewhere on the board
/Power/RSET: R38.2; also elsewhere on the board
GNDA: R38.1; also elsewhere on the board
